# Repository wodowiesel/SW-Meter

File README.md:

# SW-Meter

Custom PCB design of an external S-&amp;Watt-Meter for radios. Useful for all radio enthusiasts and amateur HAM operators.

## DISCLAIMERS

This is still "work-in-progress (WIP)" so I do NOT take any kind of warranty/responsibility for damages or data losses!

You can use this at your own risk without any guarantees and put device on non-conductive surface or enclosure!

If you like the new design you are free to share it!

Have fun and 73 :)

## HARDWARE

- 1x Custom THT PCB: (B) 66 x (L) 53 x (H) ~2 mm + ~15 mm parts height

  by WodoWiesel (wodowiesel@quantentunnel.de)

- 1x BNC male connector 50 Ohm Impedance

- 1x T-Adapter/cable for antenna/transceiver

- 1x 3.5 mm (or 2.5) audio jack female connector incl. a cable for hook up to your radio

- 1x +9 V Block Battery + 1x click connector

- 1x 330 Ohm Resistor – optional for LED

- 3x Variable Trimmer resistors 3-pins (1x1.2k & 2x4.7 kOhm)

- 1x Electrolytic Capacitor ~22 µF (pol.)

- 1x 3-pos. DIP-switch for additional signal/graph modes

- 1x On/Off-switch

- 1x 2-pos. 3-pin switch - for Input selection

- 2x DC-Volt-Meters 3-pins

- 1x Female Pin Headers/Socket - recommended for driver chip

- 1x LM3914 (linear), or 3915/16 (logarithmic dB) dot/bar display driver from Texas Instruments

  extra calculator (https://www.electro-tech-online.com/tools/LM3914V2.php)

- 1x 1N914 fast-switching Schottky Diode - to prevent backflow

- 10x LEDs (v0.5) or 1x Bar-Graph (v0.7)

- 1x M3 short flat head screw

- maybe metal case or 3D printed enclosure for isolation

- 1x Soldering iron & Screwdriver

- Solder + flux + IPA + brush + paper

- Multimeter/Oscilloscope for verification

## Credits

©️ 2022/23 WodoWiesel (https://github.com/wodowiesel/ & https://www.twitch.com/wodowiesel/)

The new design was checked by the electrical engineer theBrutzler

(https://github.com/theBrutzler/ & https://www.twitch.com/theBrutzler/)

The new optimized PCB was designed with free KiCAD software (https://www.kicad.org/)

The PCB should be produced at a manufacturer (like PCBWay) with the RoHS lead-free option for environmental protection

## LICENSE

This project is licensed under:

CERN Open Hardware License Version 2 - Weakly Reciprocal

Short identifier CERN-OHL-W-2.0

[LICENSE Source](https://spdx.org/licenses/CERN-OHL-W-2.0.html)

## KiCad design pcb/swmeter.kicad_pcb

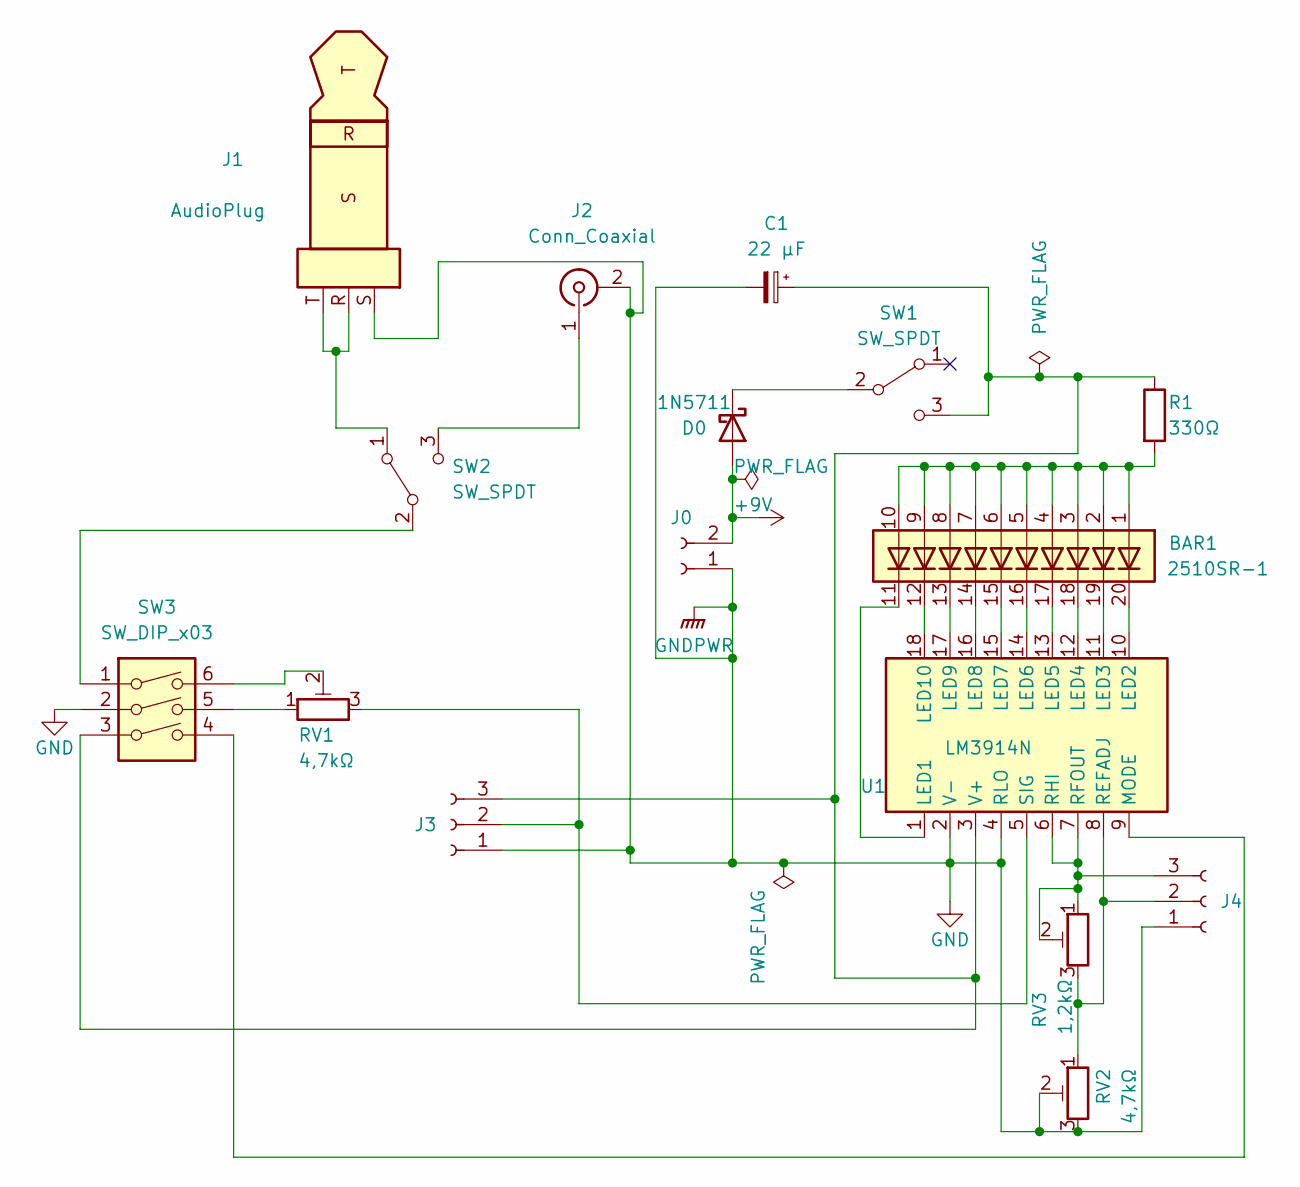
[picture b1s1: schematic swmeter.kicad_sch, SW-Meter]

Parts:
BAR1: 2510SR-1; HDSP-4836
C1: 22 µF; CP_Radial_D4.0mm_P2.00mm
D0: 1N5711; D_DO-35_SOD27_P7.62mm_Horizontal
J0: Conn_01x02_Female; PinHeader_1x02_P2.54mm_Vertical
J1: AudioPlug; Jack_3.5mm_Lumberg_1503_07_Horizontal
J2: Conn_Coaxial; BNC_TEConnectivity_1478035_Horizontal
J3, J4: Conn_01x03_Female; PinHeader_1x03_P2.54mm_Vertical
R1: 330Ω; R_Axial_DIN0207_L6.3mm_D2.5mm_P7.62mm_Horizontal
RV1, RV2: 4,7kΩ; Potentiometer_Bourns_3266Y_Vertical
RV3: 1,2kΩ; Potentiometer_Bourns_3266Y_Vertical
SW1: SW_SPDT; SW_Slide_1P2T_CK_OS102011MS2Q
SW2: SW_SPDT; SW_E-Switch_EG1224_SPDT_Angled
SW3: SW_DIP_x03; SW_DIP_SPSTx03_Slide_9.78x9.8mm_W7.62mm_P2.54mm
U1: LM3914N; DIP-18_W7.62mm_Socket

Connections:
+9V: D0.2 (A), J0.2
GND: C1.2, J0.1, J1.S, J2.2 (Ext), J3.1, J4.1, RV2.2, RV2.3, SW3.2, U1.2 (V-), U1.4 (RLO); also elsewhere on the board
unnamed: BAR1.1 (A), BAR1.2 (A), BAR1.3 (A), BAR1.4 (A), BAR1.5 (A), BAR1.6 (A), BAR1.7 (A), BAR1.8 (A), BAR1.9 (A), BAR1.10 (A), R1.2
unnamed: BAR1.11 (K), U1.1 (LED1)
unnamed: BAR1.12 (K), U1.18 (LED10)
unnamed: BAR1.13 (K), U1.17 (LED9)
unnamed: BAR1.14 (K), U1.16 (LED8)
unnamed: BAR1.15 (K), U1.15 (LED7)
unnamed: BAR1.16 (K), U1.14 (LED6)
unnamed: BAR1.17 (K), U1.13 (LED5)
unnamed: BAR1.18 (K), U1.12 (LED4)
unnamed: BAR1.19 (K), U1.11 (LED3)
unnamed: BAR1.20 (K), U1.10 (LED2)
unnamed: C1.1, J3.3, R1.1, SW1.3 (C), SW3.3, U1.3 (V+)
unnamed: D0.1 (K), SW1.2 (B)
unnamed: J1.R, J1.T, SW2.1 (A)
unnamed: J2.1 (In), SW2.3 (C)
unnamed: J3.2, RV1.3, U1.5 (SIG)
unnamed: J4.2, RV2.1, RV3.3, U1.8 (REFADJ)
unnamed: J4.3, RV3.1, RV3.2, U1.6 (RHI), U1.7 (RFOUT)
unnamed: RV1.1, SW3.5
unnamed: RV1.2, SW3.6
unnamed: SW2.2 (B), SW3.1
unnamed: SW3.4, U1.9 (MODE)

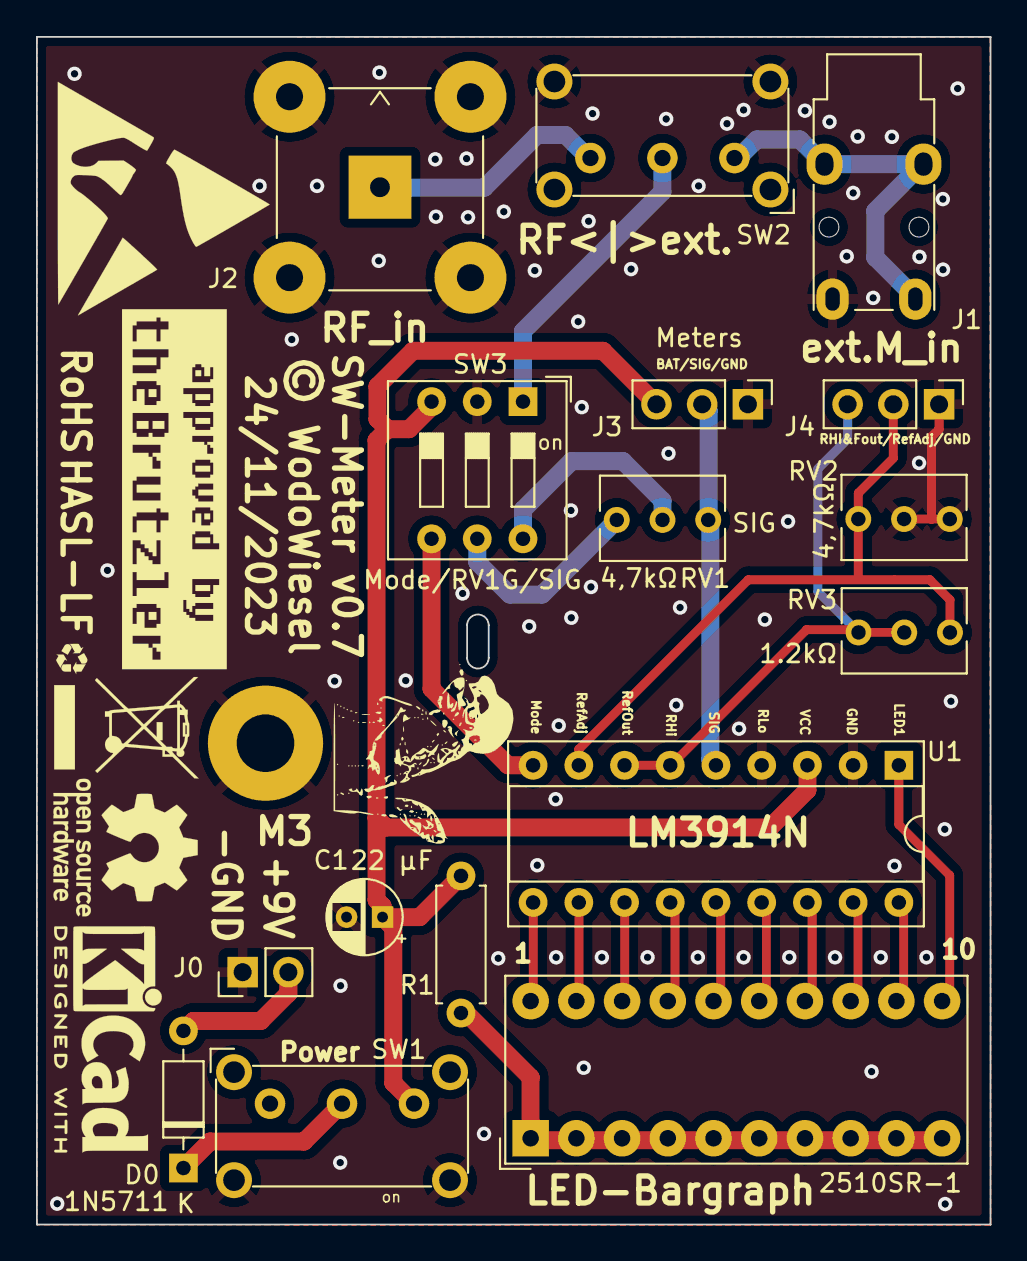
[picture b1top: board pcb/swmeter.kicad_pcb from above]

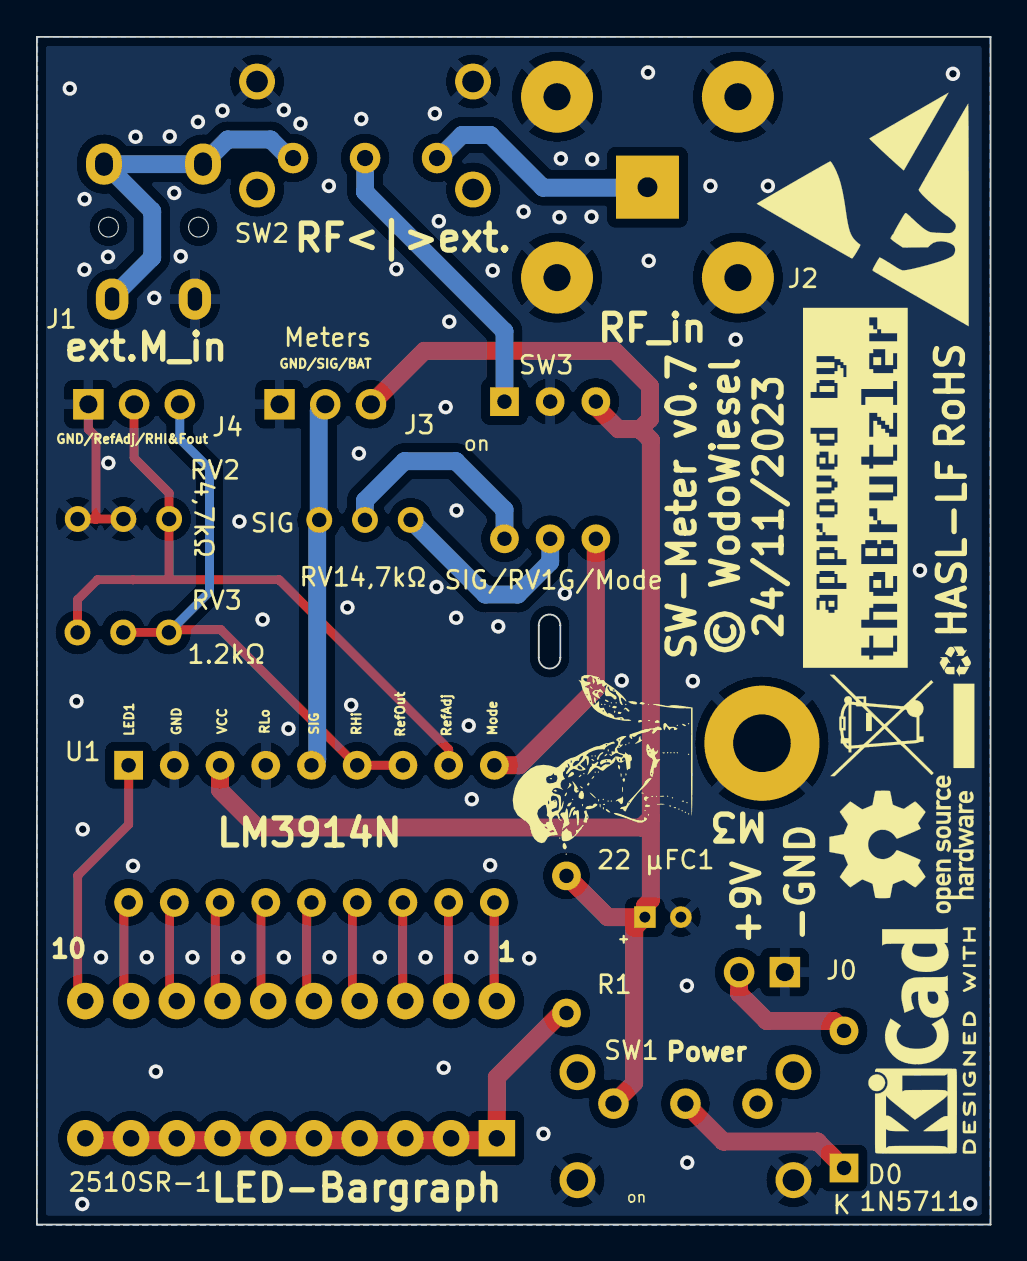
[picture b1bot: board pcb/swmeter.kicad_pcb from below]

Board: 2 copper layers, 53.0 x 66.0 mm, 31 parts (7 on the bottom side), 24 nets.

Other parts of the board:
G1, G11: LOGO; approved_theBrutzler
G2, G22: LOGO; wiesel-kicad-back-white
G9, G99: LOGO; recycling-symbol-kicad
REF0, REF00: WEEE-Logo_5.6x8mm_SilkScreen
REF3, REF33: OSHW-Logo_7.5x8mm_SilkScreen
REF7**, REF77**: ESD-Logo_13.2x12mm_SilkScreen
REF8**, REF88**: KiCad-Logo2_5mm_SilkScreen
REF99**: MountingHole_3.2mm_M3_Pad

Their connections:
GND: REF99**.1; also elsewhere on the board

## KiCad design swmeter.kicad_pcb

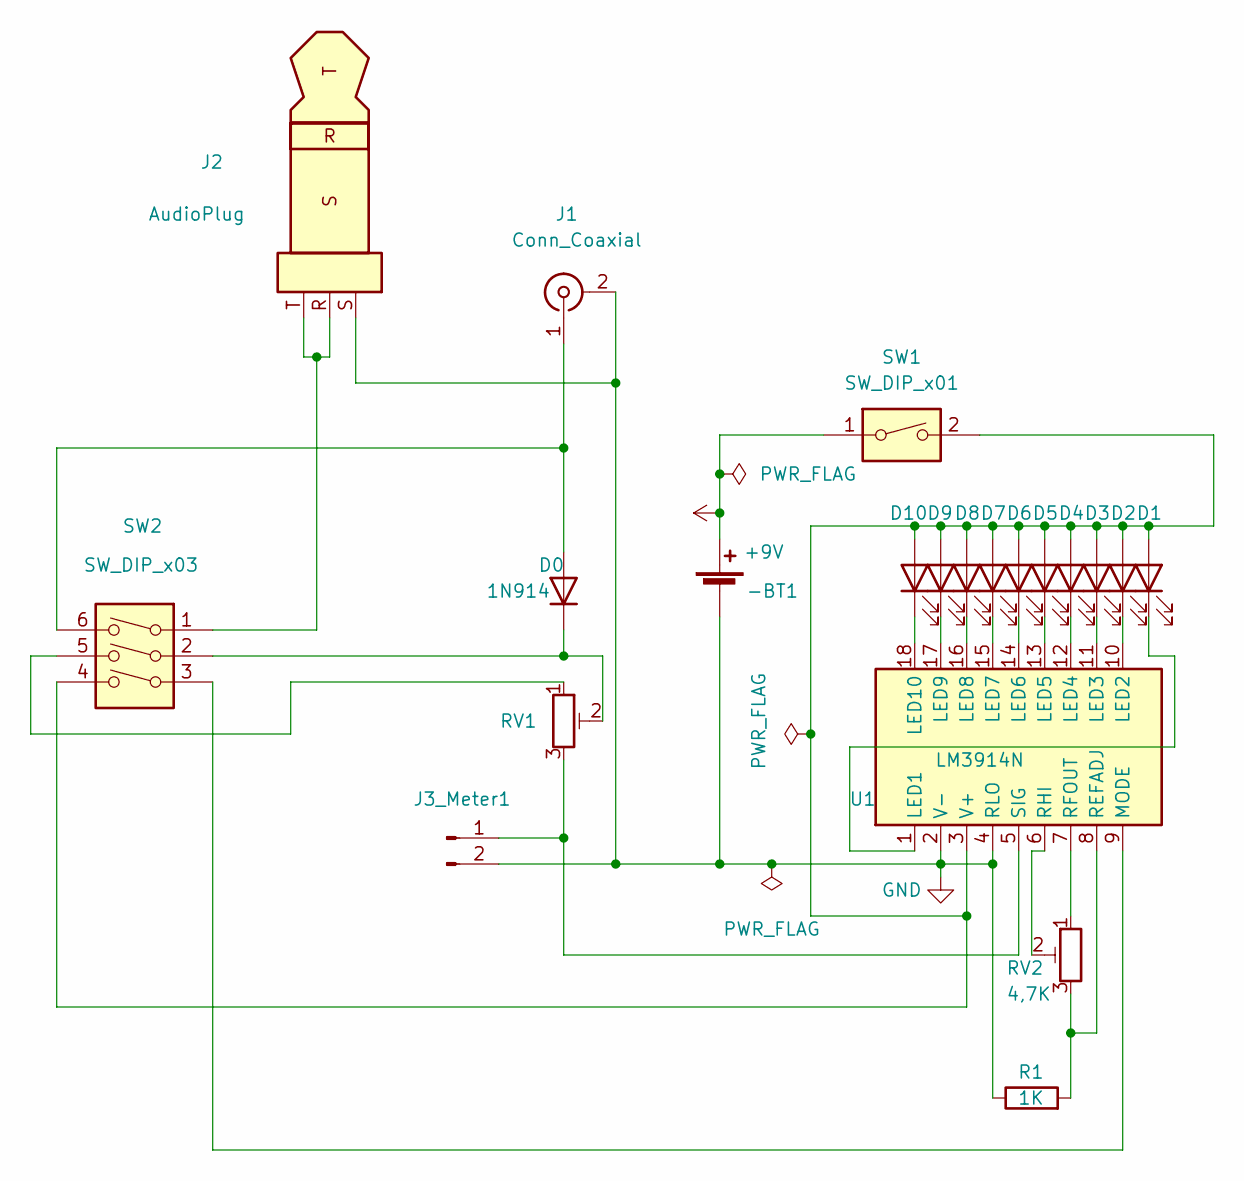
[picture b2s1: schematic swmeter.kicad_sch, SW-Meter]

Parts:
-BT1: Battery_Cell; BatteryHolder_Eagle_12BH611-GR
D0: 1N914; D_DO-35_SOD27_P7.62mm_Horizontal
D1, D2, D3, D4, D5, D6, D7, D8, D9: LED; LED_D3.0mm_Clear
D10: red; LED_D3.0mm_Clear
J1: Conn_Coaxial; BNC_TEConnectivity_1478035_Horizontal
J2: AudioPlug; Jack_3.5mm_Lumberg_1503_07_Horizontal
J3_Meter1: Conn_01x02_Male; PinHeader_1x02_P1.27mm_Vertical
R1: 1K; R_Axial_DIN0207_L6.3mm_D2.5mm_P10.16mm_Horizontal
RV1: R_Potentiometer_Trim; Potentiometer_Bourns_3266Y_Vertical
RV2: 4,7K; Potentiometer_Bourns_3266Y_Vertical
SW1: SW_DIP_x01; SW_DIP_SPSTx01_Slide_9.78x4.72mm_W7.62mm_P2.54mm
SW2: SW_DIP_x03; SW_DIP_SPSTx03_Slide_6.7x9.18mm_W7.62mm_P2.54mm_LowProfile
U1: LM3914N; DIP-18_W7.62mm_Socket

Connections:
+9V: -BT1.1 (+), SW1.1
GND: -BT1.2 (-), J1.2 (Ext), J2.S, J3_Meter1.2, R1.1, U1.2 (V-), U1.4 (RLO)
unnamed: D0.1 (K), RV1.2, SW2.2
unnamed: D0.2 (A), J1.1 (In), SW2.6
unnamed: D1.1 (K), U1.1 (LED1)
unnamed: D1.2 (A), D2.2 (A), D3.2 (A), D4.2 (A), D5.2 (A), D6.2 (A), D7.2 (A), D8.2 (A), D9.2 (A), D10.2 (A), SW1.2, SW2.4, U1.3 (V+)
unnamed: D2.1 (K), U1.10 (LED2)
unnamed: D3.1 (K), U1.11 (LED3)
unnamed: D4.1 (K), U1.12 (LED4)
unnamed: D5.1 (K), U1.13 (LED5)
unnamed: D6.1 (K), U1.14 (LED6)
unnamed: D7.1 (K), U1.15 (LED7)
unnamed: D8.1 (K), U1.16 (LED8)
unnamed: D9.1 (K), U1.17 (LED9)
unnamed: D10.1 (K), U1.18 (LED10)
unnamed: J2.R, J2.T, SW2.1
unnamed: J3_Meter1.1, RV1.3, U1.5 (SIG)
unnamed: R1.2, RV2.3, U1.8 (REFADJ)
unnamed: RV1.1, SW2.5
unnamed: RV2.1, U1.7 (RFOUT)
unnamed: RV2.2, U1.6 (RHI)
unnamed: SW2.3, U1.9 (MODE)

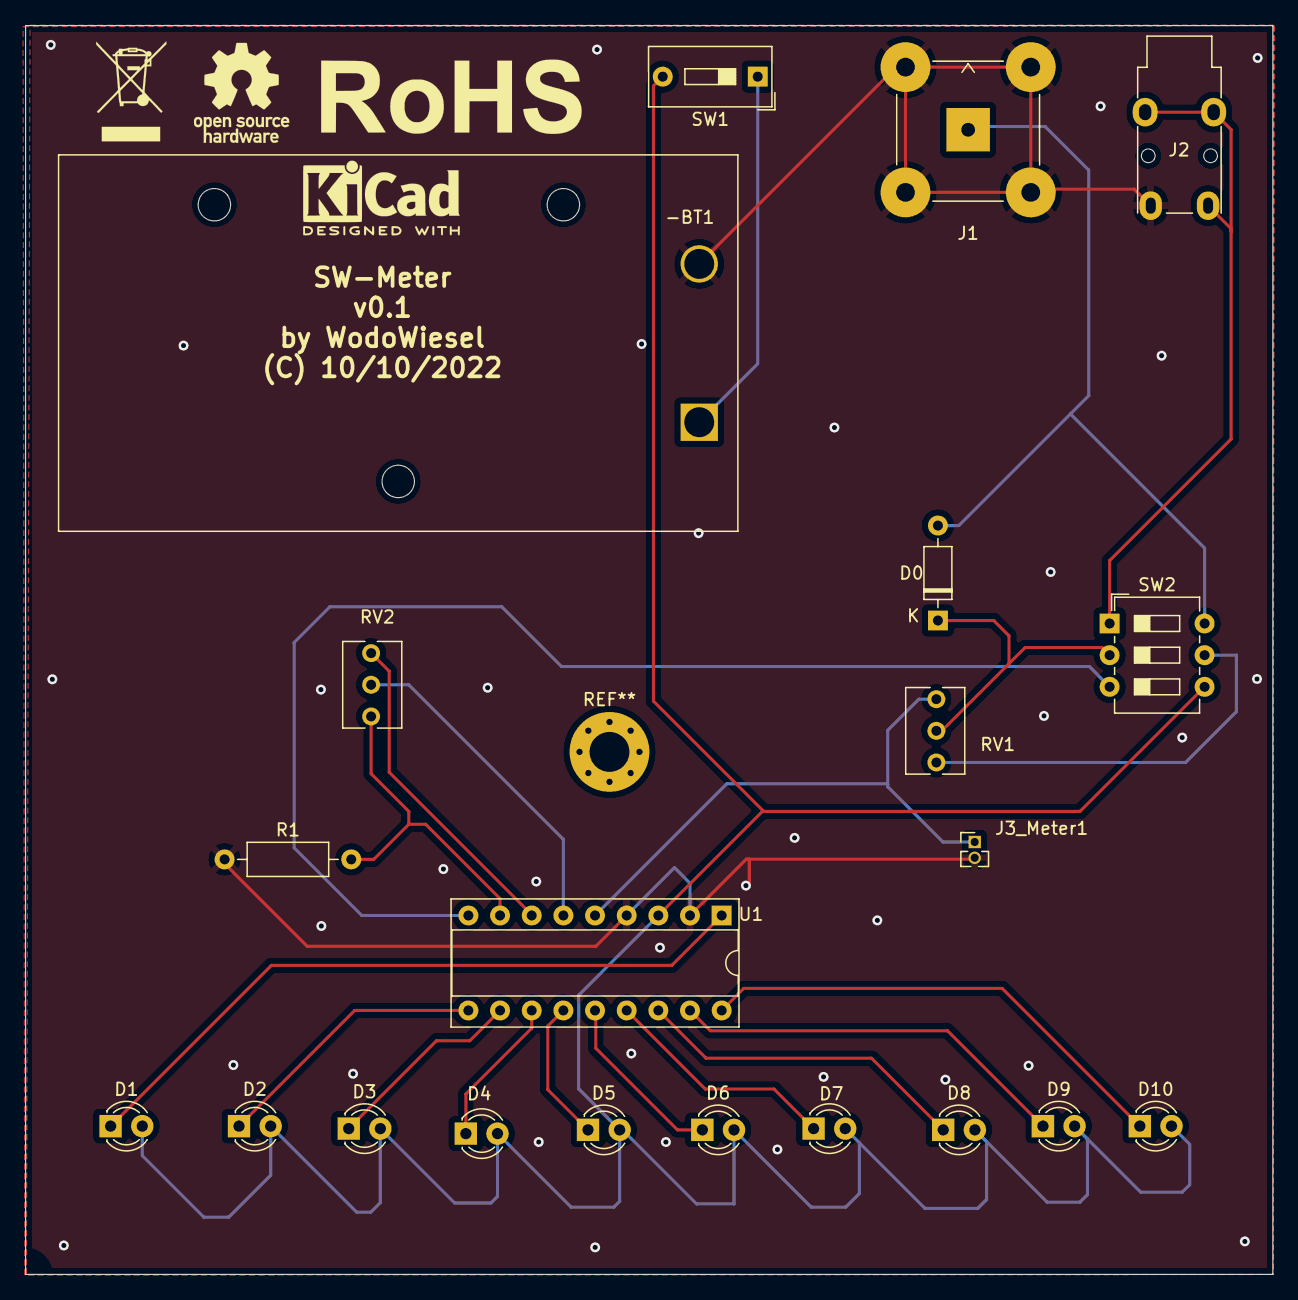
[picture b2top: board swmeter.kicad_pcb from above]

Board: 2 copper layers, 100.1 x 100.2 mm, 21 parts (0 on the bottom side), 22 nets.

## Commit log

2022-10-08 initial upload PCB design
    initial upload PCB design
2022-10-08 LICENSE.md
    LICENSE.md
2022-10-08 docs+readme update
2022-10-09 clanup
2022-10-09 shhapes-parts
2022-10-12 design optimizations by adding input switch
2022-10-15 Update README.md
    changed Impedance infos
2022-10-21 Opimizations - prettify Silkscreens & Routings - DC-Meter 3-Pin Hheader - Gerber & Layer Files
2022-10-23 more Infos
    more Infos
2022-10-28 Update README.md
    additional infos for parts
2022-10-28 clean up folders
2022-11-06 Update README.md
    Add cap info
2022-11-07 schematics update
2022-11-07 export update
2022-11-15 -double trace width -use 2 same switches -add recycling logo -add HASL info -optimize gnd-plane
2022-12-17 make pretty
2023-03-04 improve readability
    improve readability
2023-06-07 remove bckup spam
2023-10-13 -update to compact bargraph design -add capacitor for battery
2023-10-13 updated docs
2023-10-13 update 3d pcb png
2023-10-22 -mounting with gnd -removed orientation crosses
2023-10-22 update docs with new pcb layout
2023-10-22 -export layers -export gerber
2023-12-27 optimized trimmer schematics
    optimized trimmer schematics
2023-12-27 add diode for reverse polarity protection

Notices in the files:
pcb/swmeter.kicad_pcb:
© WodoWiesel
